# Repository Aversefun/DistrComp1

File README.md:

# DistrComp1
Thing built around 128-256 dirt cheap MCUs

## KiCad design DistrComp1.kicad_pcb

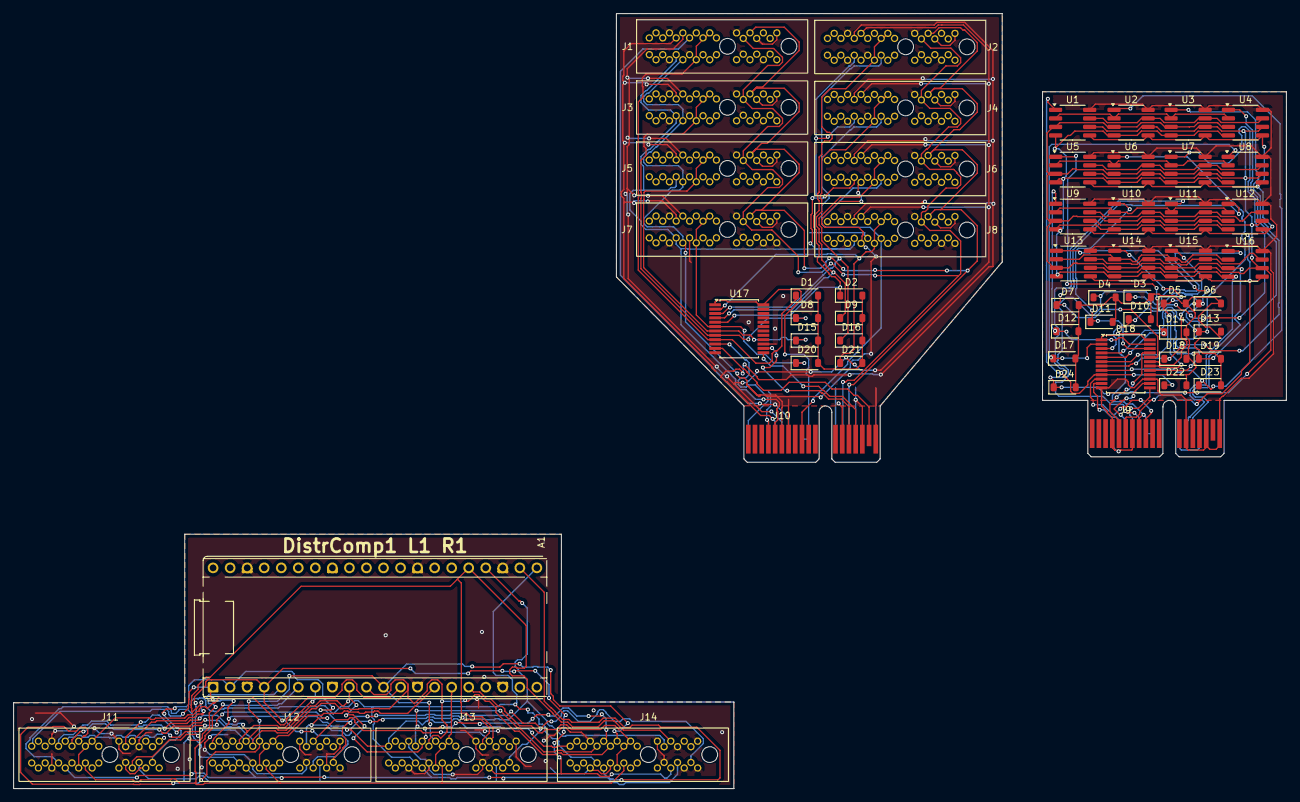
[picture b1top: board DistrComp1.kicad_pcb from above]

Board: 2 copper layers, 189.7 x 115.5 mm, 57 parts (0 on the bottom side), 75 nets.

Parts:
A1: RaspberryPi_Pico; RaspberryPi_Pico_Common_THT
D1, D2, D3, D4, D5, D6, D7, D8, D9, D10, D11, D12, D13, D14, D15, D16, D17, D18, D19, D20, D21, D22, D23, D24: D_Schottky; D_SOD-123
J1, J2, J3, J4, J5, J6, J7, J8, J11, J12, J13, J14: Bus_PCI_Express_x1; PCIexpress_HYCW05-PCI36-155B
J9, J10: Bus_PCI_Express_x1; BUS_PCIexpress_x1
U1, U2, U3, U4, U5, U6, U7, U8, U9, U10, U11, U12, U13, U14, U15, U16: NY8A054ES8; SOP-8_3.76x4.96mm_P1.27mm
U17, U18: CD74HC4067SM; SSOP-24_5.3x8.2mm_P0.65mm

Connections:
/Blade/+3V3: J9.A9 (+3.3V), J9.A10 (+3.3V), J9.B8 (+3.3V), U18.1 (COM), U18.24 (VCC)
/Blade/CC0: U1.7 (PA2), U2.7 (PA2), U3.7 (PA2), U4.7 (PA2)
/Blade/CC1: U5.7 (PA2), U6.7 (PA2), U7.7 (PA2), U8.7 (PA2)
/Blade/CC2: U9.7 (PA2), U10.7 (PA2), U11.7 (PA2), U12.7 (PA2)
/Blade/CC3: U13.7 (PA2), U14.7 (PA2), U15.7 (PA2), U16.7 (PA2)
/Blade/CD0: U1.2 (PA7), U2.2 (PA7), U3.2 (PA7), U4.2 (PA7)
/Blade/CD1: U5.2 (PA7), U6.2 (PA7), U7.2 (PA7), U8.2 (PA7)
/Blade/CD2: U9.2 (PA7), U10.2 (PA7), U11.2 (PA7), U12.2 (PA7)
/Blade/CD3: U13.2 (PA7), U14.2 (PA7), U15.2 (PA7), U16.2 (PA7)
/Blade/E0: D22.1 (K), U1.1 (VDD), U18.9 (I0)
/Blade/E1: D23.1 (K), U2.1 (VDD), U18.8 (I1)
/Blade/E2: D18.1 (K), U3.1 (VDD), U18.7 (I2)
/Blade/E3: D19.1 (K), U4.1 (VDD), U18.6 (I3)
/Blade/E4: D14.1 (K), U5.1 (VDD), U18.5 (I4)
/Blade/E5: D13.1 (K), U6.1 (VDD), U18.4 (I5)
/Blade/E6: D10.1 (K), U7.1 (VDD), U18.3 (I6)
/Blade/E7: D17.1 (K), U8.1 (VDD), U18.2 (I7)
/Blade/E8: D12.1 (K), U9.1 (VDD), U18.23 (I8)
/Blade/E9: D11.1 (K), U10.1 (VDD), U18.22 (I9)
/Blade/E10: D24.1 (K), U11.1 (VDD), U18.21 (I10)
/Blade/E11: D7.1 (K), U12.1 (VDD), U18.20 (I11)
/Blade/E12: D6.1 (K), U13.1 (VDD), U18.19 (I12)
/Blade/E13: D5.1 (K), U14.1 (VDD), U18.18 (I13)
/Blade/E14: D3.1 (K), U15.1 (VDD), U18.17 (I14)
/Blade/E15: D4.1 (K), J9.A8 (JTAG5), U16.1 (VDD)
/Blade/PA3: J9.B5 (SMCLK), U1.6 (PA3), U2.6 (PA3), U3.6 (PA3), U4.6 (PA3), U5.6 (PA3), U6.6 (PA3), U7.6 (PA3), U8.6 (PA3), U9.6 (PA3), U10.6 (PA3), U11.6 (PA3), U12.6 (PA3), U13.6 (PA3), U14.6 (PA3), U15.6 (PA3), U16.6 (PA3)
/Blade/PA4: J9.B6 (SMDAT), U1.5 (PA4), U2.5 (PA4), U3.5 (PA4), U4.5 (PA4), U5.5 (PA4), U6.5 (PA4), U7.5 (PA4), U8.5 (PA4), U9.5 (PA4), U10.5 (PA4), U11.5 (PA4), U12.5 (PA4), U13.5 (PA4), U14.5 (PA4), U15.5 (PA4), U16.5 (PA4)
/Blade/PA5: J9.A13 (REFCLK+), U1.4 (PA5), U2.4 (PA5), U3.4 (PA5), U4.4 (PA5), U5.4 (PA5), U6.4 (PA5), U7.4 (PA5), U8.4 (PA5), U9.4 (PA5), U10.4 (PA5), U11.4 (PA5), U12.4 (PA5), U13.4 (PA5), U14.4 (PA5), U15.4 (PA5), U16.4 (PA5)
/Blade/PA6: J9.A14 (REFCLK-), U1.3 (PA6), U2.3 (PA6), U3.3 (PA6), U4.3 (PA6), U5.3 (PA6), U6.3 (PA6), U7.3 (PA6), U8.3 (PA6), U9.3 (PA6), U10.3 (PA6), U11.3 (PA6), U12.3 (PA6), U13.3 (PA6), U14.3 (PA6), U15.3 (PA6), U16.3 (PA6)
/SheathL0/+3V3: J10.A9 (+3.3V), J10.A10 (+3.3V), J10.B8 (+3.3V), U17.1 (COM), U17.24 (VCC)
/SheathL0/Be0: J10.A1 (~PRSNT1), U17.10 (S0)
/SheathL0/Be1: J10.B17 (~PRSNT2), U17.11 (S1)
/SheathL0/Be2: J10.B14 (PETp0), U17.14 (S2)
/SheathL0/Be3: J10.B15 (PETn0), U17.13 (S3)
/SheathL0/E0: D1.1 (K), J1.A9 (+3.3V), J1.A10 (+3.3V), J1.B8 (+3.3V), U17.9 (I0)
/SheathL0/E1: D8.1 (K), J3.A9 (+3.3V), J3.A10 (+3.3V), J3.B8 (+3.3V), U17.8 (I1)
/SheathL0/E2: D15.1 (K), J5.A9 (+3.3V), J5.A10 (+3.3V), J5.B8 (+3.3V), U17.7 (I2)
/SheathL0/E3: D20.1 (K), J7.A9 (+3.3V), J7.A10 (+3.3V), J7.B8 (+3.3V), U17.6 (I3)
/SheathL0/E4: D2.1 (K), J2.A9 (+3.3V), J2.A10 (+3.3V), J2.B8 (+3.3V), U17.5 (I4)
/SheathL0/E5: D9.1 (K), J4.A9 (+3.3V), J4.A10 (+3.3V), J4.B8 (+3.3V), U17.4 (I5)
/SheathL0/E6: D16.1 (K), J6.A9 (+3.3V), J6.A10 (+3.3V), J6.B8 (+3.3V), U17.3 (I6)
/SheathL0/E7: D21.1 (K), J8.A9 (+3.3V), J8.A10 (+3.3V), J8.B8 (+3.3V), U17.2 (I7)
/SheathL0/En0: J1.B9 (JTAG1), J2.B9 (JTAG1), J3.B9 (JTAG1), J4.B9 (JTAG1), J5.B9 (JTAG1), J6.B9 (JTAG1), J7.B9 (JTAG1), J8.B9 (JTAG1), J10.B9 (JTAG1)
/SheathL0/En1: J1.A5 (JTAG2), J2.A5 (JTAG2), J3.A5 (JTAG2), J4.A5 (JTAG2), J5.A5 (JTAG2), J6.A5 (JTAG2), J7.A5 (JTAG2), J8.A5 (JTAG2), J10.A5 (JTAG2)
/SheathL0/En2: J1.A6 (JTAG3), J2.A6 (JTAG3), J3.A6 (JTAG3), J4.A6 (JTAG3), J5.A6 (JTAG3), J6.A6 (JTAG3), J7.A6 (JTAG3), J8.A6 (JTAG3), J10.A6 (JTAG3)
/SheathL0/En3: J1.A7 (JTAG4), J2.A7 (JTAG4), J3.A7 (JTAG4), J4.A7 (JTAG4), J5.A7 (JTAG4), J6.A7 (JTAG4), J7.A7 (JTAG4), J8.A7 (JTAG4), J10.A7 (JTAG4)
/SheathL0/En15: J1.A8 (JTAG5), J2.A8 (JTAG5), J3.A8 (JTAG5), J4.A8 (JTAG5), J5.A8 (JTAG5), J6.A8 (JTAG5), J7.A8 (JTAG5), J8.A8 (JTAG5), J10.A8 (JTAG5)
/SheathL0/PA3: J1.B5 (SMCLK), J2.B5 (SMCLK), J3.B5 (SMCLK), J4.B5 (SMCLK), J5.B5 (SMCLK), J6.B5 (SMCLK), J7.B5 (SMCLK), J8.B5 (SMCLK), J10.B5 (SMCLK)
/SheathL0/PA4: J1.B6 (SMDAT), J2.B6 (SMDAT), J3.B6 (SMDAT), J4.B6 (SMDAT), J5.B6 (SMDAT), J6.B6 (SMDAT), J7.B6 (SMDAT), J8.B6 (SMDAT), J10.B6 (SMDAT)
/SheathL0/PA5: J1.A13 (REFCLK+), J2.A13 (REFCLK+), J3.A13 (REFCLK+), J4.A13 (REFCLK+), J5.A13 (REFCLK+), J6.A13 (REFCLK+), J7.A13 (REFCLK+), J8.A13 (REFCLK+), J10.A13 (REFCLK+)
/SheathL0/PA6: J1.A14 (REFCLK-), J2.A14 (REFCLK-), J3.A14 (REFCLK-), J4.A14 (REFCLK-), J5.A14 (REFCLK-), J6.A14 (REFCLK-), J7.A14 (REFCLK-), J8.A14 (REFCLK-), J10.A14 (REFCLK-)
/SheathL1/Be0: A1.1 (GPIO0), J11.A1 (~PRSNT1), J12.A1 (~PRSNT1), J13.A1 (~PRSNT1), J14.A1 (~PRSNT1)
/SheathL1/Be1: A1.2 (GPIO1), J11.B17 (~PRSNT2), J12.B17 (~PRSNT2), J13.B17 (~PRSNT2), J14.B17 (~PRSNT2)
/SheathL1/Be2: A1.4 (GPIO2), J11.B14 (PETp0), J12.B14 (PETp0), J13.B14 (PETp0), J14.B14 (PETp0)
/SheathL1/Be3: A1.5 (GPIO3), J11.B15 (PETn0), J12.B15 (PETn0), J13.B15 (PETn0), J14.B15 (PETn0)
/SheathL1/En0: A1.6 (GPIO4), J11.B9 (JTAG1), J12.B9 (JTAG1), J13.B9 (JTAG1), J14.B9 (JTAG1)
/SheathL1/En1: A1.7 (GPIO5), J11.A5 (JTAG2), J12.A5 (JTAG2), J13.A5 (JTAG2), J14.A5 (JTAG2)
/SheathL1/En2: A1.9 (GPIO6), J11.A6 (JTAG3), J12.A6 (JTAG3), J13.A6 (JTAG3), J14.A6 (JTAG3)
/SheathL1/En3: A1.10 (GPIO7), J11.A7 (JTAG4), J12.A7 (JTAG4), J13.A7 (JTAG4), J14.A7 (JTAG4)
/SheathL1/En15: A1.11 (GPIO8), J11.A8 (JTAG5), J12.A8 (JTAG5), J13.A8 (JTAG5), J14.A8 (JTAG5)
/SheathL1/PA3: A1.21 (GPIO16), J11.B5 (SMCLK), J12.B5 (SMCLK), J13.B5 (SMCLK), J14.B5 (SMCLK)
/SheathL1/PA4: A1.22 (GPIO17), J11.B6 (SMDAT), J12.B6 (SMDAT), J13.B6 (SMDAT), J14.B6 (SMDAT)
/SheathL1/PA5: A1.24 (GPIO18), J11.A13 (REFCLK+), J12.A13 (REFCLK+), J13.A13 (REFCLK+), J14.A13 (REFCLK+)
/SheathL1/PA6: A1.25 (GPIO19), J11.A14 (REFCLK-), J12.A14 (REFCLK-), J13.A14 (REFCLK-), J14.A14 (REFCLK-)
/SheathL1/S0: A1.12 (GPIO9), J11.A9 (+3.3V), J11.A10 (+3.3V), J11.B8 (+3.3V)
/SheathL1/S1: A1.14 (GPIO10), J12.A9 (+3.3V), J12.A10 (+3.3V), J12.B8 (+3.3V)
/SheathL1/S2: A1.15 (GPIO11), J13.A9 (+3.3V), J13.A10 (+3.3V), J13.B8 (+3.3V)
/SheathL1/S3: A1.16 (GPIO12), J14.A9 (+3.3V), J14.A10 (+3.3V), J14.B8 (+3.3V)
GND: A1.3 (GND), A1.8 (GND), A1.13 (GND), A1.18 (GND), A1.23 (GND), A1.28 (GND), A1.38 (GND), J1.A4 (GND), J1.A12 (GND), J1.A15 (GND), J1.A18 (GND), J1.B4 (GND), J1.B7 (GND), J1.B13 (GND), J1.B16 (GND), J1.B18 (GND), J2.A4 (GND), J2.A12 (GND), J2.A15 (GND), J2.A18 (GND), J2.B4 (GND), J2.B7 (GND), J2.B13 (GND), J2.B16 (GND), J2.B18 (GND), J3.A4 (GND), J3.A12 (GND), J3.A15 (GND), J3.A18 (GND), J3.B4 (GND), J3.B7 (GND), J3.B13 (GND), J3.B16 (GND), J3.B18 (GND), J4.A4 (GND), J4.A12 (GND), J4.A15 (GND), J4.A18 (GND), J4.B4 (GND), J4.B7 (GND), J4.B13 (GND), J4.B16 (GND), J4.B18 (GND), J5.A4 (GND), J5.A12 (GND), J5.A15 (GND), J5.A18 (GND), J5.B4 (GND), J5.B7 (GND), J5.B13 (GND), J5.B16 (GND), J5.B18 (GND), J6.A4 (GND), J6.A12 (GND), J6.A15 (GND), J6.A18 (GND), J6.B4 (GND), J6.B7 (GND), J6.B13 (GND), J6.B16 (GND), J6.B18 (GND), J7.A4 (GND), J7.A12 (GND), J7.A15 (GND), J7.A18 (GND), J7.B4 (GND), J7.B7 (GND), J7.B13 (GND), J7.B16 (GND), J7.B18 (GND), J8.A4 (GND), J8.A12 (GND), J8.A15 (GND), J8.A18 (GND), J8.B4 (GND), J8.B7 (GND), J8.B13 (GND), J8.B16 (GND), J8.B18 (GND), J9.A4 (GND), J9.A12 (GND), J9.A15 (GND), J9.A18 (GND), J9.B4 (GND), J9.B7 (GND), J9.B13 (GND), J9.B16 (GND), J9.B18 (GND), J10.A4 (GND), J10.A12 (GND), J10.A15 (GND), J10.A18 (GND), J10.B4 (GND), J10.B7 (GND), J10.B13 (GND), J10.B16 (GND), J10.B18 (GND), J11.A4 (GND), J11.A12 (GND), J11.A15 (GND), J11.A18 (GND), J11.B4 (GND), J11.B7 (GND), J11.B13 (GND), J11.B16 (GND), J11.B18 (GND), J12.A4 (GND), J12.A12 (GND), J12.A15 (GND), J12.A18 (GND), J12.B4 (GND), J12.B7 (GND), J12.B13 (GND), J12.B16 (GND), J12.B18 (GND), J13.A4 (GND), J13.A12 (GND), J13.A15 (GND), J13.A18 (GND), J13.B4 (GND), J13.B7 (GND), J13.B13 (GND), J13.B16 (GND), J13.B18 (GND), J14.A4 (GND), J14.A12 (GND), J14.A15 (GND), J14.A18 (GND), J14.B4 (GND), J14.B7 (GND), J14.B13 (GND), J14.B16 (GND), J14.B18 (GND), U1.8 (VSS), U2.8 (VSS), U3.8 (VSS), U4.8 (VSS), U5.8 (VSS), U6.8 (VSS), U7.8 (VSS), U8.8 (VSS), U9.8 (VSS), U10.8 (VSS), U11.8 (VSS), U12.8 (VSS), U13.8 (VSS), U14.8 (VSS), U15.8 (VSS), U16.8 (VSS), U17.12 (GND), U17.15 (~E), U18.12 (GND), U18.15 (~E)
unnamed: D1.2 (A), D2.2 (A), D8.2 (A), D9.2 (A), D15.2 (A), D16.2 (A), D20.2 (A), D21.2 (A), U17.16 (I15)
unnamed: D3.2 (A), D4.2 (A), D5.2 (A), D6.2 (A), D7.2 (A), D10.2 (A), D11.2 (A), D12.2 (A), D13.2 (A), D14.2 (A), D17.2 (A), D18.2 (A), D19.2 (A), D22.2 (A), D23.2 (A), D24.2 (A), U18.16 (I15)
unnamed: J9.B9 (JTAG1), U18.10 (S0)
unnamed: J9.A5 (JTAG2), U18.11 (S1)
unnamed: J9.A6 (JTAG3), U18.14 (S2)
unnamed: J9.A7 (JTAG4), U18.13 (S3)

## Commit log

2025-07-19 Create LICENSE
2025-08-05 add stuff
2025-08-05 add .envrc for direnv
